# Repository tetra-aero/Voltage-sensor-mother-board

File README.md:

# Voltage-sensor-mother-board
voltage sensor INA238 module mother board

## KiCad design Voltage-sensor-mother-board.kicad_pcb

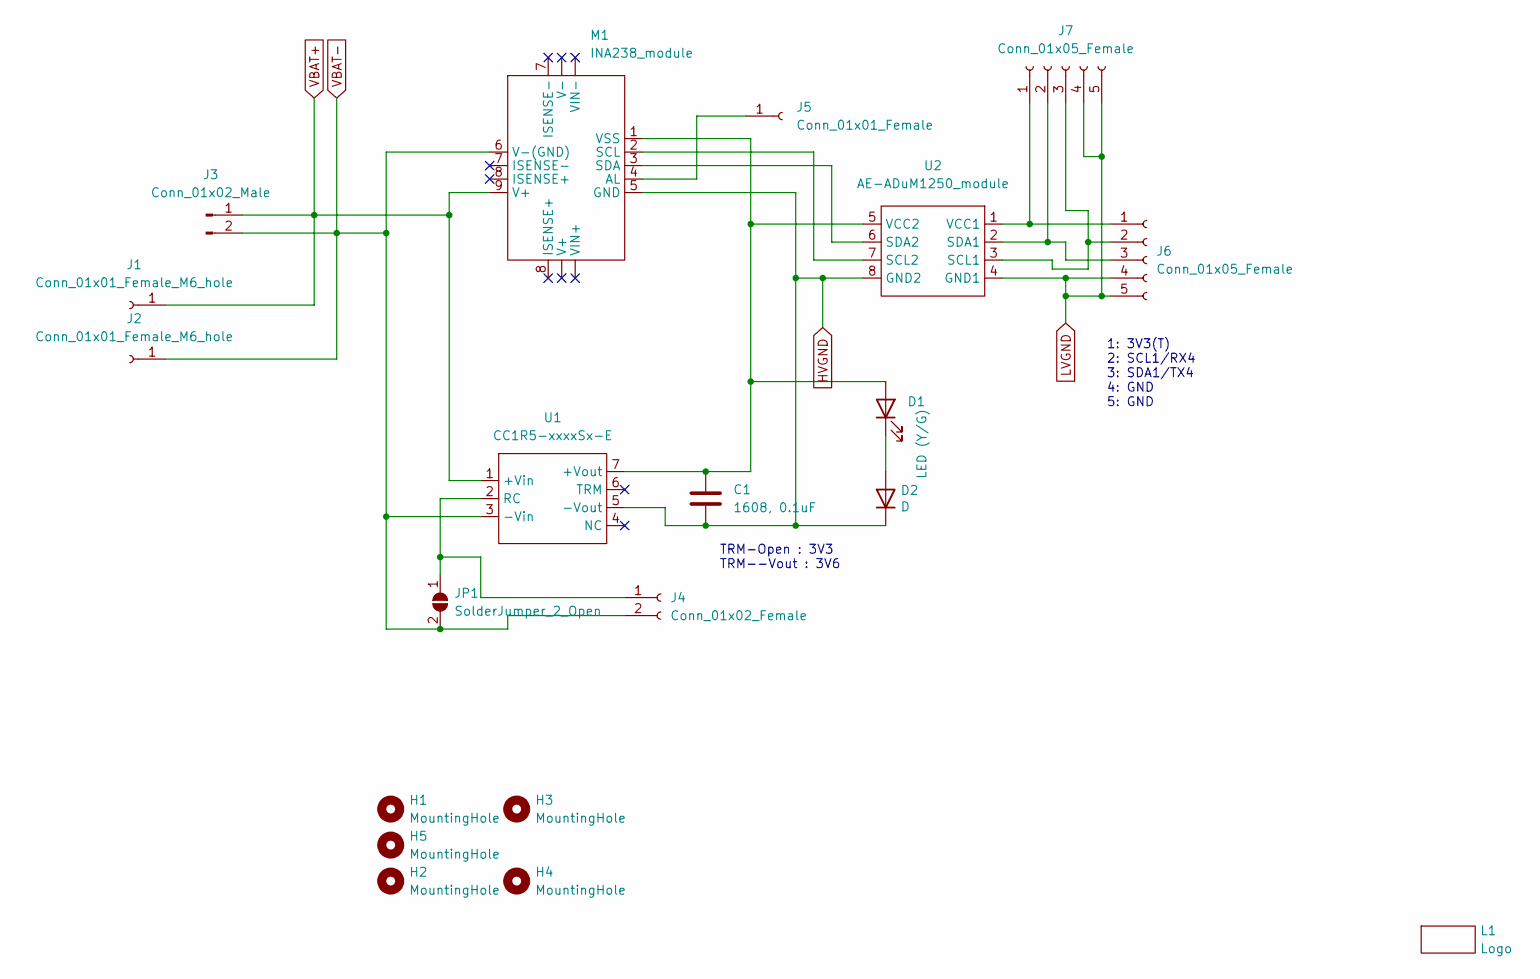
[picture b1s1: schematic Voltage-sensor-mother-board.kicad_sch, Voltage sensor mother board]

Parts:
C1: 1608, 0.1uF; C_0603_1608Metric_Pad1.08x0.95mm_HandSolder
D1: LED (Y/G); LED_0603_1608Metric_Pad1.05x0.95mm_HandSolder
D2: D; CRD_S_Series
H1, H2, H3, H4, H5: MountingHole; MountingHole_3.2mm_M3_ISO7380
J1, J2: Conn_01x01_Female_M6_hole; MountingHole_6.4mm_M6_Pad_TopBottom
J3: Conn_01x02_Male; JST_VH_B2P-VH-B_1x02_P3.96mm_Vertical
J4: Conn_01x02_Female; JST_XH_B2B-XH-A_1x02_P2.50mm_Vertical
J5: Conn_01x01_Female; PinHeader_1x01_P2.54mm_Vertical
J6: Conn_01x05_Female; PinHeader_1x05_P2.54mm_Vertical
J7: Conn_01x05_Female; JST_XH_B5B-XH-A_1x05_P2.50mm_Vertical
JP1: SolderJumper_2_Open; SolderJumper-2_P1.3mm_Open_Pad1.0x1.5mm
L1: Logo; teTra-logo
M1: INA238_module
U1: CC1R5-xxxxSx-E; CC1R5-4803SR-E
U2: AE-ADuM1250_module

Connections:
HVGND: C1.2, D2.1 (K), M1.5 (GND), U1.5 (-Vout), U2.8 (GND2)
LVGND: J6.4, J6.5, J7.4, J7.5, U2.4 (GND1)
unnamed: C1.1, D1.2 (A), M1.1 (VSS), U1.7 (+Vout), U2.5 (VCC2)
unnamed: D1.1 (K), D2.2 (A)
unnamed: J4.1, JP1.1 (A), U1.2 (RC)
unnamed: J5.1, M1.4 (AL)
unnamed: J6.1, J7.1, U2.1 (VCC1)
unnamed: J6.2, J7.3, U2.3 (SCL1)
unnamed: J6.3, J7.2, U2.2 (SDA1)
unnamed: M1.2 (SCL), U2.7 (SCL2)
unnamed: M1.3 (SDA), U2.6 (SDA2)
VBAT+: J1.1, J3.1, M1.9 (V+), U1.1 (+Vin)
VBAT-: J2.1, J3.2, J4.2, JP1.2 (B), M1.6 (V-(GND)), U1.3 (-Vin)

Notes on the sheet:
1: 3V3(T) 2: SCL1/RX4 3: SDA1/TX4 4: GND 5: GND
TRM-Open : 3V3 TRM--Vout : 3V6

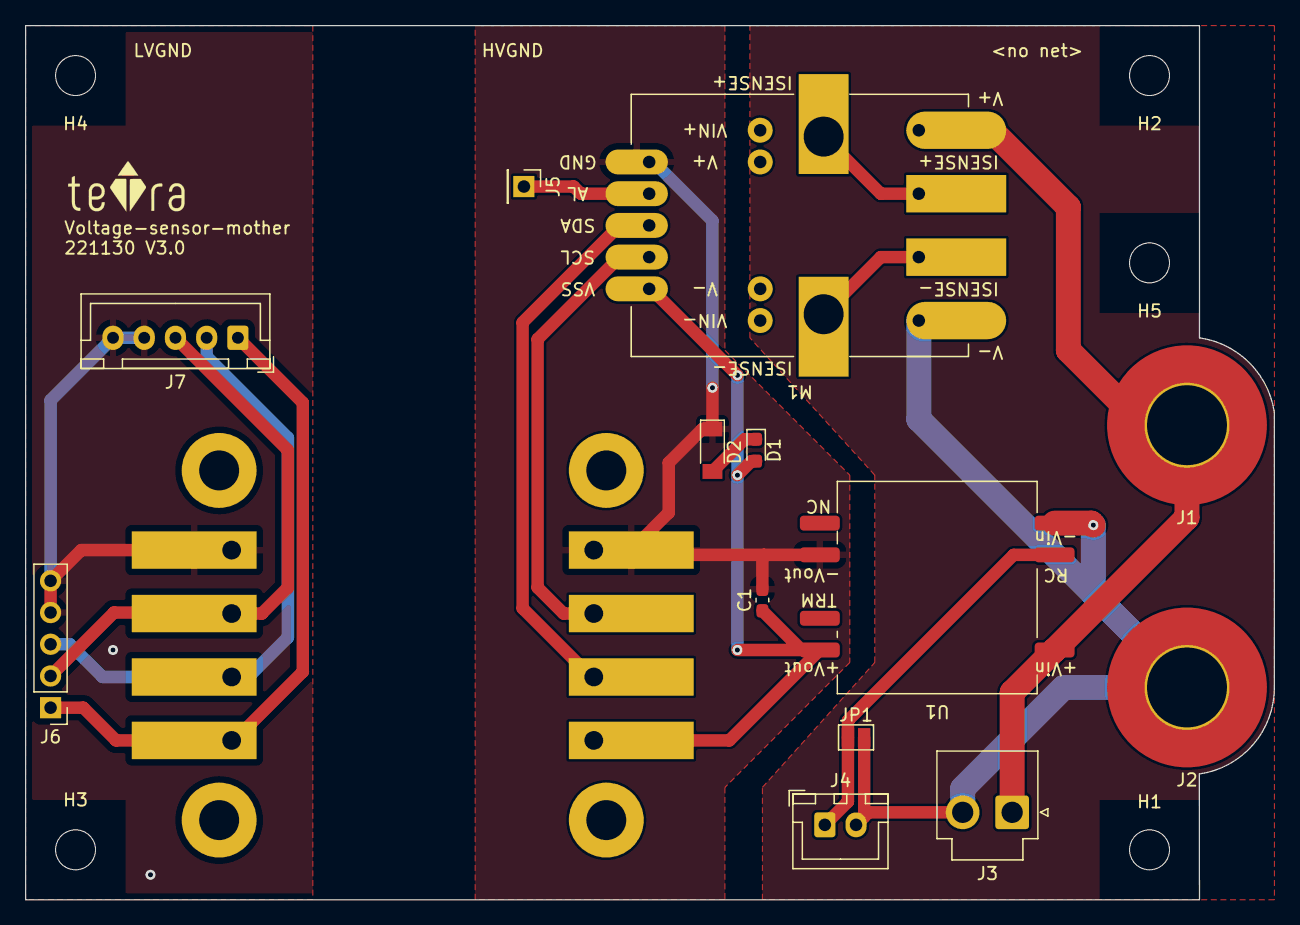
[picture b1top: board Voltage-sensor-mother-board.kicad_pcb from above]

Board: 2 copper layers, 100.0 x 70.0 mm, 20 parts (1 on the bottom side), 13 nets.

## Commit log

2022-11-02 add v2.0
    add v2.0
2022-11-30 add v3.0
    add v3.0
